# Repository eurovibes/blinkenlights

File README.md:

<!-- SPDX-FileCopyrightText: 2021 Benedikt Spranger <b.spranger@linutronix.de> -->
<!-- SPDX-License-Identifier: CERN-OHL-S-2.0 -->

# blinkenlights - A ESP based LED backlight

## License rules

blinkenlights is provided under the terms of the CERN-OHL-S license version 2
as provided in the LICENSES/CERN-OHL-S-2.0 file.

Instead of adding license boilerplates to the individual files, blinkenlights
uses SPDX license identifiers, which are machine parseable and considered
legaly equivalent.

The SPDX license identifier in blinkenlights shall be added at the first
possible line in a file which can contain a comment. This is normally the
first line except for scripts. Scripts require the #!PATH_TO_INTERPRETER tag
in the first line; place the SPDX identifier into the second line.

The SPDX license identifier is added in form of a comment.

## Copyright and License

> Copyright Benedikt Spranger 2021.
> This source describes Open Hardware and is licensed under the CERNOHL-S v2.
> You may redistribute and modify this source and make products using it
> under the terms of the CERN-OHL-S v2 (https://ohwr.org/cern ohl s v2.txt).
> This source is distributed WITHOUT ANY EXPRESS OR IMPLIED WARRANTY, INCLUDING
> OF MERCHANTABILITY, SATISFACTORY QUALITY AND FITNESS FOR A PARTICULAR PURPOSE.
> Please see the CERN-OHL-S v2 for applicable conditions.
> Source location: https://github.com/eurovibes/blinkenlights
> As per CERN-OHL-S v2 section 4, should You produce hardware based
> on this source, You must where practicable maintain the Source Location
> visible on the external case of the blinkenlights or other products you make
> using this source.

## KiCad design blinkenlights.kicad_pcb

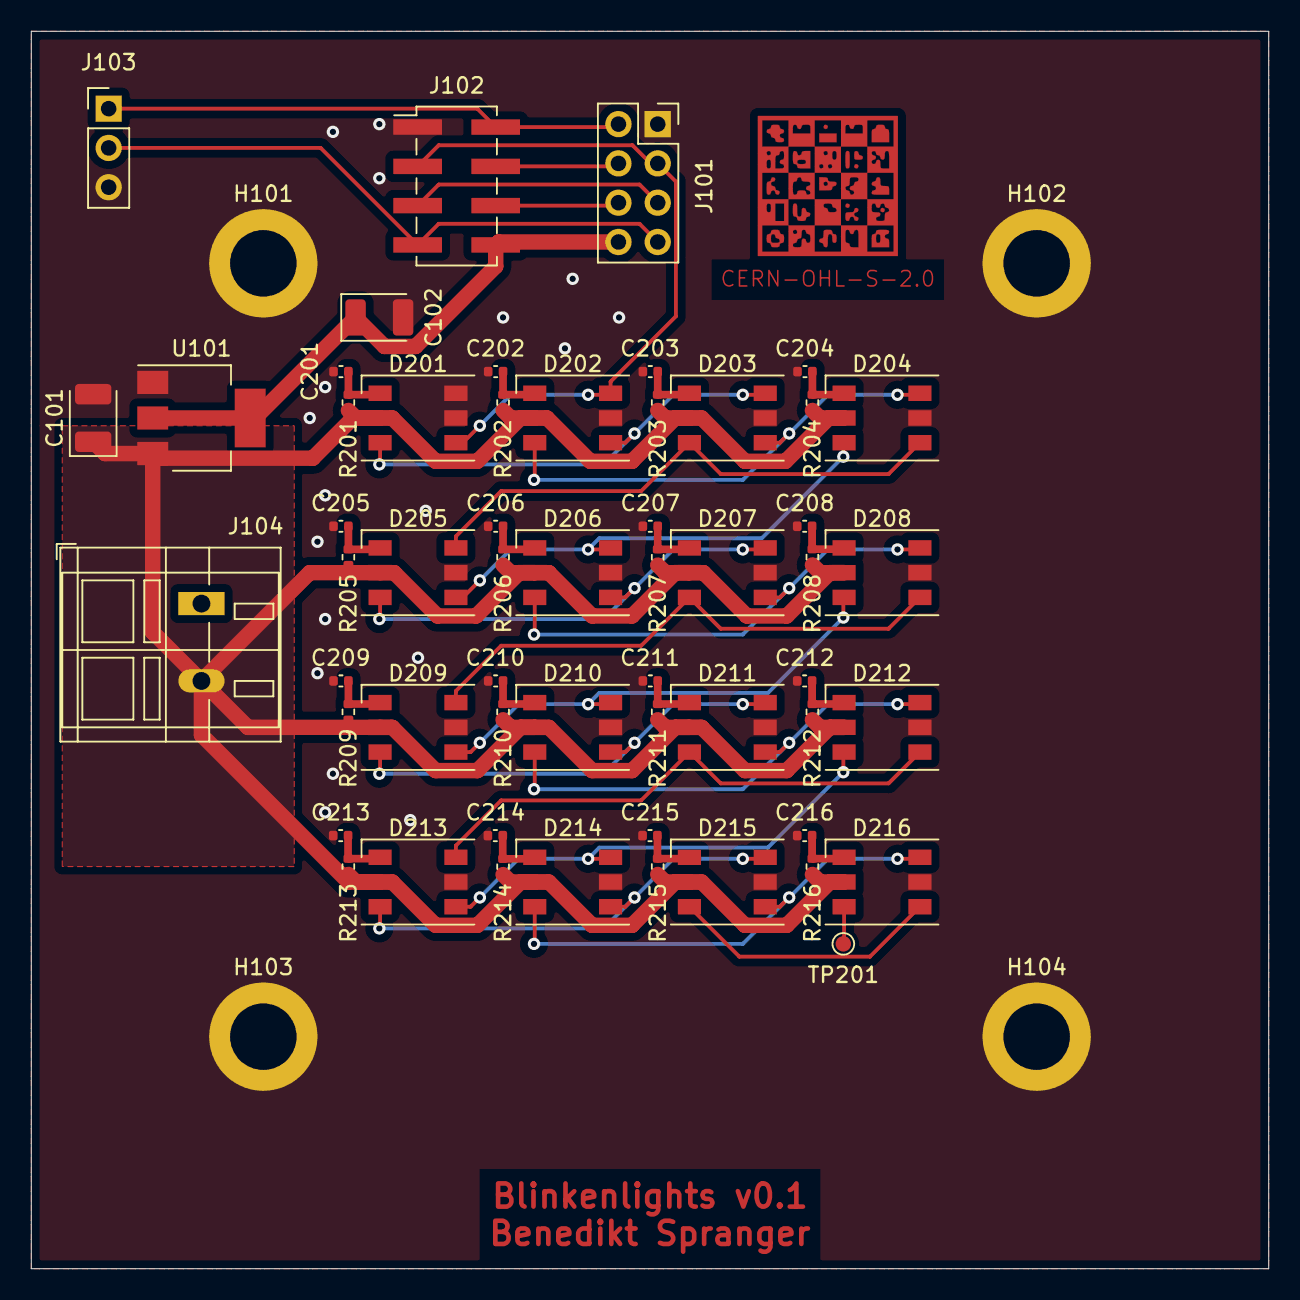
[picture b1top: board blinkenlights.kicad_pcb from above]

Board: 2 copper layers, 80.0 x 80.0 mm, 60 parts (0 on the bottom side), 41 nets.

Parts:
C101, C102: 22µ; CP_EIA-3528-21_Kemet-B
C201, C202, C203, C204, C205, C206, C207, C208, C209, C210, C211, C212, C213, C214, C215, C216: 100n; C_0402_1005Metric
D201, D202, D203, D204, D205, D206, D207, D208, D209, D210, D211, D212, D213, D214, D215, D216: WS2813; LED_WS2812_PLCC6_5.0x5.0mm_P1.6mm
H101, H102, H103, H104: MountingHole_4.3mm_M4_ISO14580_Pad
J101: ESP-01S; PinSocket_2x04_P2.54mm_Vertical
J102: PROG; PinHeader_2x04_P2.54mm_Vertical_SMD
J103: serial; PinHeader_1x03_P2.54mm_Vertical
J104: PWR; TerminalBlock_WAGO_236-102_1x02_P5.00mm_45Degree
R201, R202, R203, R204, R205, R206, R207, R208, R209, R210, R211, R212, R213, R214, R215, R216: 150; R_0402_1005Metric
TP201: TestPoint; TestPoint_Pad_D1.0mm
U101: AZ1117-3.3; SOT-223-3_TabPin2

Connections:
+3V3: C102.1, J101.8, J102.8, U101.2
+5V: C101.1, D201.2, D202.2, D203.2, D204.2, D205.2, D206.2, D207.2, D208.2, D209.2, D210.2, D211.2, D212.2, D213.2, D214.2, D215.2, D216.2, J104.2, R201.1, R202.1, R203.1, R204.1, R205.1, R206.1, R207.1, R208.1, R209.1, R210.1, R211.1, R212.1, R213.1, R214.1, R215.1, R216.1, U101.3
/IO0: J101.5, J102.5
/IO2: D201.4, D202.6, J101.3, J102.3
/LEDS/DO1: D208.3, D209.4, D210.6
/LEDS/DO2: D207.3, D208.4, D209.6
/RX: J101.7, J102.7, J103.2
/TX: J101.2, J102.2, J103.1
GND: C101.2, C102.2, C201.1, C202.1, C203.1, C204.1, C205.1, C206.1, C207.1, C208.1, C209.1, C210.1, C211.1, C212.1, C213.1, C214.1, C215.1, C216.1, D201.5, D201.6, D202.5, D203.5, D204.5, D205.5, D206.5, D207.5, D208.5, D209.5, D210.5, D211.5, D212.5, D213.5, D214.5, D215.5, D216.5, H101.1, H102.1, H103.1, H104.1, J101.1, J102.1, J103.3, J104.1, U101.1
unnamed: C201.2, D201.1, R201.2
unnamed: C202.2, D202.1, R202.2
unnamed: C203.2, D203.1, R203.2
unnamed: C204.2, D204.1, R204.2
unnamed: C205.2, D205.1, R205.2
unnamed: C206.2, D206.1, R206.2
unnamed: C207.2, D207.1, R207.2
unnamed: C208.2, D208.1, R208.2
unnamed: C209.2, D209.1, R209.2
unnamed: C210.2, D210.1, R210.2
unnamed: C211.2, D211.1, R211.2
unnamed: C212.2, D212.1, R212.2
unnamed: C213.2, D213.1, R213.2
unnamed: C214.2, D214.1, R214.2
unnamed: C215.2, D215.1, R215.2
unnamed: C216.2, D216.1, R216.2
unnamed: D201.3, D202.4, D203.6
unnamed: D202.3, D203.4, D204.6
unnamed: D203.3, D204.4, D205.6
unnamed: D204.3, D205.4, D206.6
unnamed: D205.3, D206.4, D207.6
unnamed: D206.3, D207.4, D208.6
unnamed: D209.3, D210.4, D211.6
unnamed: D210.3, D211.4, D212.6
unnamed: D211.3, D212.4, D213.6
unnamed: D212.3, D213.4, D214.6
unnamed: D213.3, D214.4, D215.6
unnamed: D214.3, D215.4, D216.6
unnamed: D215.3, D216.4
unnamed: D216.3, TP201.1
unnamed: J101.4, J102.4
unnamed: J101.6, J102.6

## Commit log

2021-09-24 Initial gh page
    Add gh pages for project documentation.
2021-09-24 Deploying to gh-pages from @ eurovibes/blinkenlights@603aca5f3a8689163a74a2da5e565d334351b1a8 🚀
2021-09-24 Deploying to gh-pages from @ eurovibes/blinkenlights@5b1e340cce2e1077f0c61afdc4b4c33345d24300 🚀
2021-09-24 Konvert to KiCAD 6.x
    KiCAD 6.x use a different file format and differetn file extentions
    to store the data. Convert files to KiCAD 6.x.
